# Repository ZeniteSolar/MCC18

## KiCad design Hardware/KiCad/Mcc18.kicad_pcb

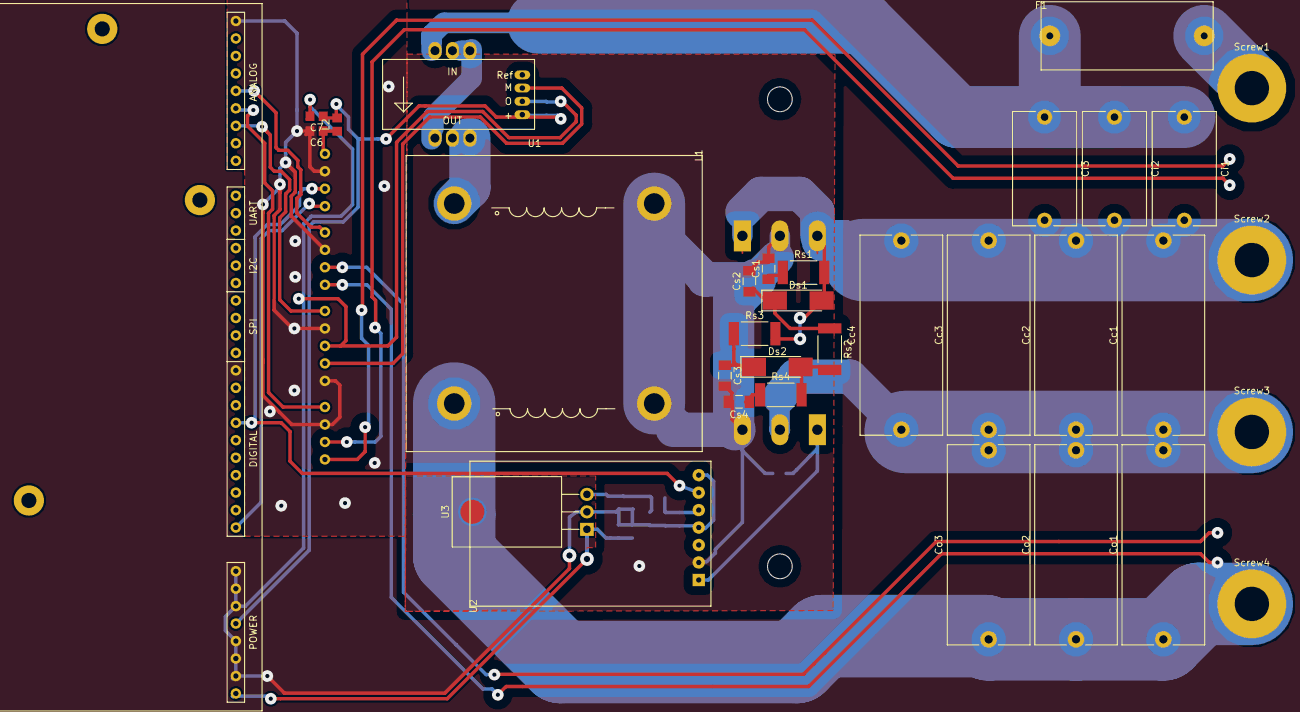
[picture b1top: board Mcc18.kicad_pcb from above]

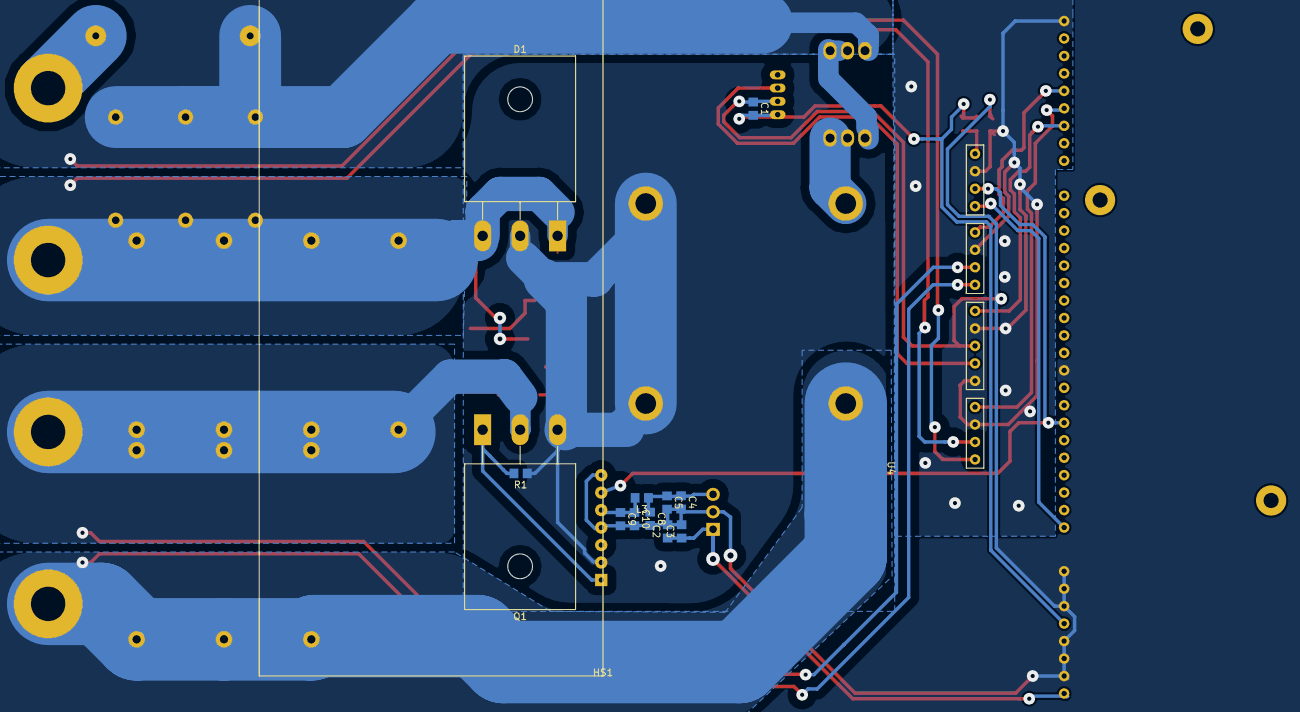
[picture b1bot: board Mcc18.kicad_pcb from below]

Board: 2 copper layers, 47 parts (14 on the bottom side), 26 nets.

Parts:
C1, C3, C4, C6, C7, C8, C9: 100nF; C_0805_2012Metric_Pad1.29x1.40mm_HandSolder
C2, C5, C10: 10uF; C_0805_2012Metric_Pad1.29x1.40mm_HandSolder
Cc1, Cc2, Cc3, Cc4: 6.8uF; C_Rect_L29.0mm_W11.9mm_P27.50mm_MKT
Ci1, Ci2, Ci3: 4.7uF; C_Rect_L16.5mm_W9.2mm_P15.00mm_MKT
Co1, Co2, Co3: 4.7uF; C_Rect_L29.0mm_W11.9mm_P27.50mm_MKT
Cs1, Cs2, Cs3, Cs4: ??; C_1206_3216Metric_Pad1.39x1.80mm_HandSolder
D1: 80CPQ150PbF; TO-247-3_Horizontal_TabUp
Ds1, Ds2: BYD77; D_MELF_Handsoldering
F1: Fuse; Porta_Fusivel
HS1: Heatsink; hs10425
L1: 50uH/50uH; NEE-42-20-DE
L2, L3: L_Small; L_0805_2012Metric_Pad1.29x1.40mm_HandSolder
Q1: IRFP4321PbF; TO-247-3_Horizontal_TabUp
R1: 10k; R_0805_2012Metric_Pad1.29x1.40mm_HandSolder
Rs1, Rs2, Rs3, Rs4: ??; R_2512_6332Metric_Pad1.49x3.40mm_HandSolder
Screw1: -P; MountingHole_5mm_Pad
Screw2: +P; MountingHole_5mm_Pad
Screw3: -B; MountingHole_5mm_Pad
Screw4: +B; MountingHole_5mm_Pad
U1: LTSP_25-NP
U2: DRIVER_(INEP); Driver_(INEP)
U3: LM7812_TO220; TO-220-3_Horizontal_TabDown
U4: Signals_MCC; Signals
U5: ZCS; ZCS18

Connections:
+5V: C1.2, C7.1, L2.2, U1.7, U5.5
+5VA: C6.1, L2.1, U4.17
+12V: C4.1, C5.1, C8.1, L3.1, U3.3
/+18V_OUT: C2.1, C3.1, U3.1, U5.1
/+B: Co1.1, Co2.1, Co3.1, L1.3, Screw4.1, U4.10
/+Vp: Cc1.2, Cc2.2, Cc3.2, Cc4.2, Ci1.2, Ci2.2, Ci3.2, D1.1, D1.3, Ds1.2, Rs1.2, Rs3.2, Screw2.1, U4.2
/-B: Cc1.1, Cc2.1, Cc3.1, Cc4.1, Co1.2, Co2.2, Co3.2, Ds2.2, Q1.2, Rs2.2, Rs4.2, Screw3.1, U4.11
/-P_unfused: F1.2, Screw1.1
/-Vp: Ci1.1, Ci2.1, Ci3.1, F1.1, U1.4, U4.1
/BatOVInterrupt: U4.14, U5.9
/Gate: Q1.1, R1.2, U2.1
/Ipanel+: U1.9, U4.6
/Ipanel_adc+: U4.9, U5.31
/PWM: U2.6, U4.15, U5.15
/Source: Cs1.2, Cs2.2, Cs3.2, Cs4.2, D1.2, L1.2, L1.4, Q1.3, R1.1, U2.2
/Vbat_adc+: U4.13, U5.33
/Vpanel_adc+: U4.4, U5.32
GND: C1.1, C2.2, C3.2, C4.2, C5.2, C7.2, C8.2, C9.2, C10.2, U1.8, U2.4, U2.7, U3.2, U4.7, U5.2, U5.3, U5.4, U5.6, U5.7, U5.8, U5.18
GNDA: C6.2, U4.3, U4.5, U4.8, U4.12, U4.16, U5.37
unnamed: C9.1, C10.1, L3.2, U2.5
unnamed: Cs1.1, Rs1.1
unnamed: Cs2.1, Ds1.1, Rs2.1
unnamed: Cs3.1, Ds2.1, Rs3.1
unnamed: Cs4.1, Rs4.1
unnamed: L1.1, U1.1, U1.2
unnamed: U1.3, U1.5, U1.6
